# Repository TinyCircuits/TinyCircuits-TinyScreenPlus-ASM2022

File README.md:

# TinyCircuits TinyScreen+ Processor Board
# ASM2022 Rev4

These are the design files for the TinyCircuits ASM2022 Rev 4 PCB.  This is a Tiny processor board that use an Ateml SAMD21 microcontroller and OLED has stackable TinyShield support.  

Format is in Cadsoft Eagle format - Eagle version 6.2 was used for the original design.

#License:

Design by TinyCircuits.
All design files are released under the Creative Commons Attribution Share-Alike 3.0 License, see the following link for details: http://creativecommons.org/licenses/by-sa/3.0

All text above must be included in any redistribution or derived design

This project uses designs and concepts developed as part of the Arduino project and the LilyPad project.  The TinyCircuits design files themselves (schematics, PCB and libraries) are not directly derived from these works' design files and have been created new, however the concepts and basic architecture behind the TinyDuino and TinyLily products are derived and we thank the hard work of the organizations below for their contributions to open-source hardware:
  
Original Arduino Uno Design by Team Arduino

LilyPad Arduino Design by Leah Buechley and Sparkfun Electronics

Please support the open-source hardware community

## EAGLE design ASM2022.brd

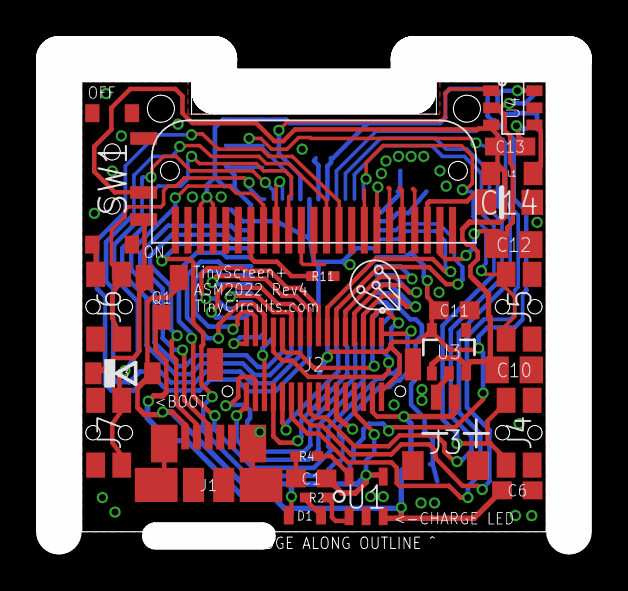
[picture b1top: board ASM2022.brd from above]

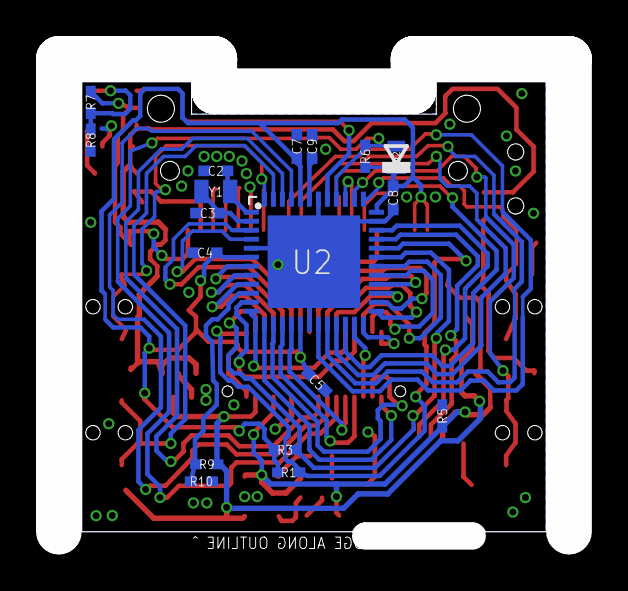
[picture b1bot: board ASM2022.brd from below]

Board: 2 copper layers, 28.3 x 26.5 mm, 45 parts (18 on the bottom side), 54 nets.

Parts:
C1, C11, C13: 10uF; C0603
C2, C3: 22pF; C0402
C4, C5, C7, C8, C9: .1uF; C0402
C6: 4.7uF; C0603
C10, C12: 10uF; C0805
C14: 4.7uF; 1206_CAP_TANT
D1: AMBER; LNJ_LED
D2: CD0603; 0603
D3: MBR120; SOD-123FL
J1: 47346-0001; MICRO_USB
J2: DF12-32-DP
J3: SM02B-SRSS; JST_SH_2X1
J4, J5, J6, J7: PTS840GKP
L1: 22uH; R0805
Q1: DMP2035U; SOT23
R1, R3, R6: 10K; 0402
R2: 1k; 0402
R4: 5K; 0402
R5: 100k; 0402
R7, R9, R10: 1.00M; 0402
R8: 16K; 0402
R11: 1.2M; 0402
SW1: PCM12SMTR
U1: MCP73831; SOT-23
U2: ATSAMD21G18A; QFN48
U3: XC6210B33; SOT-25
U4: AP3036B; SOT-23-6
U5: UG-9664HDDAG01; OLED_DISPLAY
U$1: DOCFIELD-TINYCIRCUITS-PCB
Y1: 32.7680; ABS06

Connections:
+5V: C1.1, D1.A, D3.A, J1.1, J2.8, Q1.B, R5.2, U1.4
+12V: C12.1, R7.2, U4.2, U5.22
AD0: J2.11, U2.3
AD1: J2.9, U2.7
AD2: J2.7, U2.8
AD3: J2.5, U2.9
AD4: R9.1, R10.2, U2.10
AD5: J4.1, J4.2, U2.47
AREF: J2.13, U2.4
ATN/IO38: U2.22, U5.8
DBG_RXD: J7.1, J7.2, U2.38
DBG_TXD: J6.1, J6.2, U2.37
GND: C1.2, C2.2, C3.2, C4.2, C5.2, C6.2, C7.2, C8.2, C9.2, C10.2, C11.2, C12.2, C13.2, C14.2, J1.5, J1.P1, J1.P2, J1.P3, J1.P4, J1.P5, J1.P6, J2.12, J2.14, J3.1, J4.3, J4.4, J5.3, J5.4, J6.3, J6.4, J7.3, J7.4, R4.2, R5.1, R8.1, R10.1, R11.1, SW1.W1, SW1.W2, SW1.W3, SW1.W4, U1.2, U2.5, U2.18, U2.35, U2.42, U2.EXP, U3.2, U4.5, U5.2, U5.5, U5.6, U5.11, U5.12, U5.16, U5.17, U5.18, U5.19, U5.20
IO0: J2.24, U2.16
IO1: J2.26, U2.15
IO2: J2.28, U2.23
IO3: J2.30, U2.14
IO4: J2.32, U2.13
IO5: J2.31, U2.24
IO6: J2.29, U2.29
IO7: J2.27, U2.30
IO8: J2.25, U2.11
IO9: J2.23, U2.12
MISO: J2.17, U2.28
MISO_ALT: U2.21, U5.10
MOSI: J2.19, U2.25
MOSI_ALT: U2.19, U5.14
unnamed: C2.1, U2.1, Y1.1
unnamed: D3.C, Q1.E, SW1.3
unnamed: C3.1, U2.2, Y1.2
unnamed: L1.2, U4.4
unnamed: D1.C, R2.1
unnamed: R4.1, U1.5
unnamed: R2.2, U1.1
unnamed: C9.1, U2.43
unnamed: R11.2, U5.7
unnamed: C14.1, U5.21
RESET: D2.A, J2.22, R6.1, U2.40
RX_LED/IO25/AIN11: J5.1, J5.2, U2.48
SCK: J2.15, U2.26
SCK_ALT: U2.20, U5.13
SCL: J2.1, R1.1, U2.32
SDA: J2.3, R3.1, U2.31
SS: J2.21, U2.27
SWCLK: J2.20, U2.45
SWDIO: J2.18, U2.46
TX_LED/IO26: U2.39, U5.9
USB_HOST_EN/IO27: U2.41, U4.1
USB_N: J1.2, U2.33
USB_P: J1.3, U2.34
VBATT: C6.1, J2.4, J3.2, Q1.C, R9.2, U1.3
VCC: C4.1, C5.1, C7.1, C8.1, C11.1, D2.C, J2.2, R1.2, R3.2, R6.2, U2.6, U2.17, U2.36, U2.44, U3.5, U5.3, U5.4
VCC_IN: C10.1, C13.1, L1.1, SW1.2, U3.1, U3.3, U4.3
V_FB: R7.1, R8.2, U4.6

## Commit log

2016-02-02 :tada: Added .gitattributes & .gitignore files
2017-06-08 Adding examples
    Adding example sketch to run .TSV files on the TS+.
2017-10-03 Update to Rev 4 PCB
2019-01-01 update design format
2019-01-02 update files
2019-01-07 updated comments
2019-01-11 add pictures
2019-05-22 added images
2019-05-31 added animation
2019-08-26 added correct OLED datasheet
2020-02-11 image update
2020-06-26 Add CAD data
2020-06-30 Rename files, add dxf, and use new 2D drawing template
2020-07-01 Remove vias in models & drawings, add compact dimension images, and remove file to reduce size
2020-07-02 Add zip of all CAD files
2020-08-13 new button example
2020-08-18 Update CAD drawings
